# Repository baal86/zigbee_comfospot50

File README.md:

# Zigbee Comfospot 50
Hardware module to integrate Comfospot 50 ventilation system with ESP32-H2 zigbee enabled controller. Heavily based on https://github.com/lorenzspenger/comfospot-50 but using the ESP32-H2 and Zigbee.

## Hardware 
Contains a Kicad project to produce the hardware module that plugs inbetwen the Comfospot 50 main board and the user interface panel.

> The latest change to the hardware (shortening the PCB for mechanical fit) was not tested in production. I used a previous revision PCB and shortened it with a file. I will probably never produce the latest version.

## ESPHome
Contains the .yaml file to build the firmware using ESPHome. The `partitions_zb.csv` file is required at the time of writing for zigbee support! OTA is not supported by esphome-zigbee so the image must be programmed using a USB to serial (3.3V TTL levels) converter.

## zigbee2mqtt
Contains the external converter than needs to be provided to Zigbee2MQTT to recognize the device and present it to home assistant. It is currently very basic but is working and the fan unit can be controlled by selecting the desired step.

## TODO
Honestly, it works for me as is right now so don't expect any updates soon. Debugging is quite a pain due to the lack of OTA updates and wireless logging. What I could imagine:

- Support the filter change LED
- More advanced control of fan levels as in https://github.com/lorenzspenger/comfospot-50. My implementation is quite primitive.
- Support control of exhaust/circulation modes.

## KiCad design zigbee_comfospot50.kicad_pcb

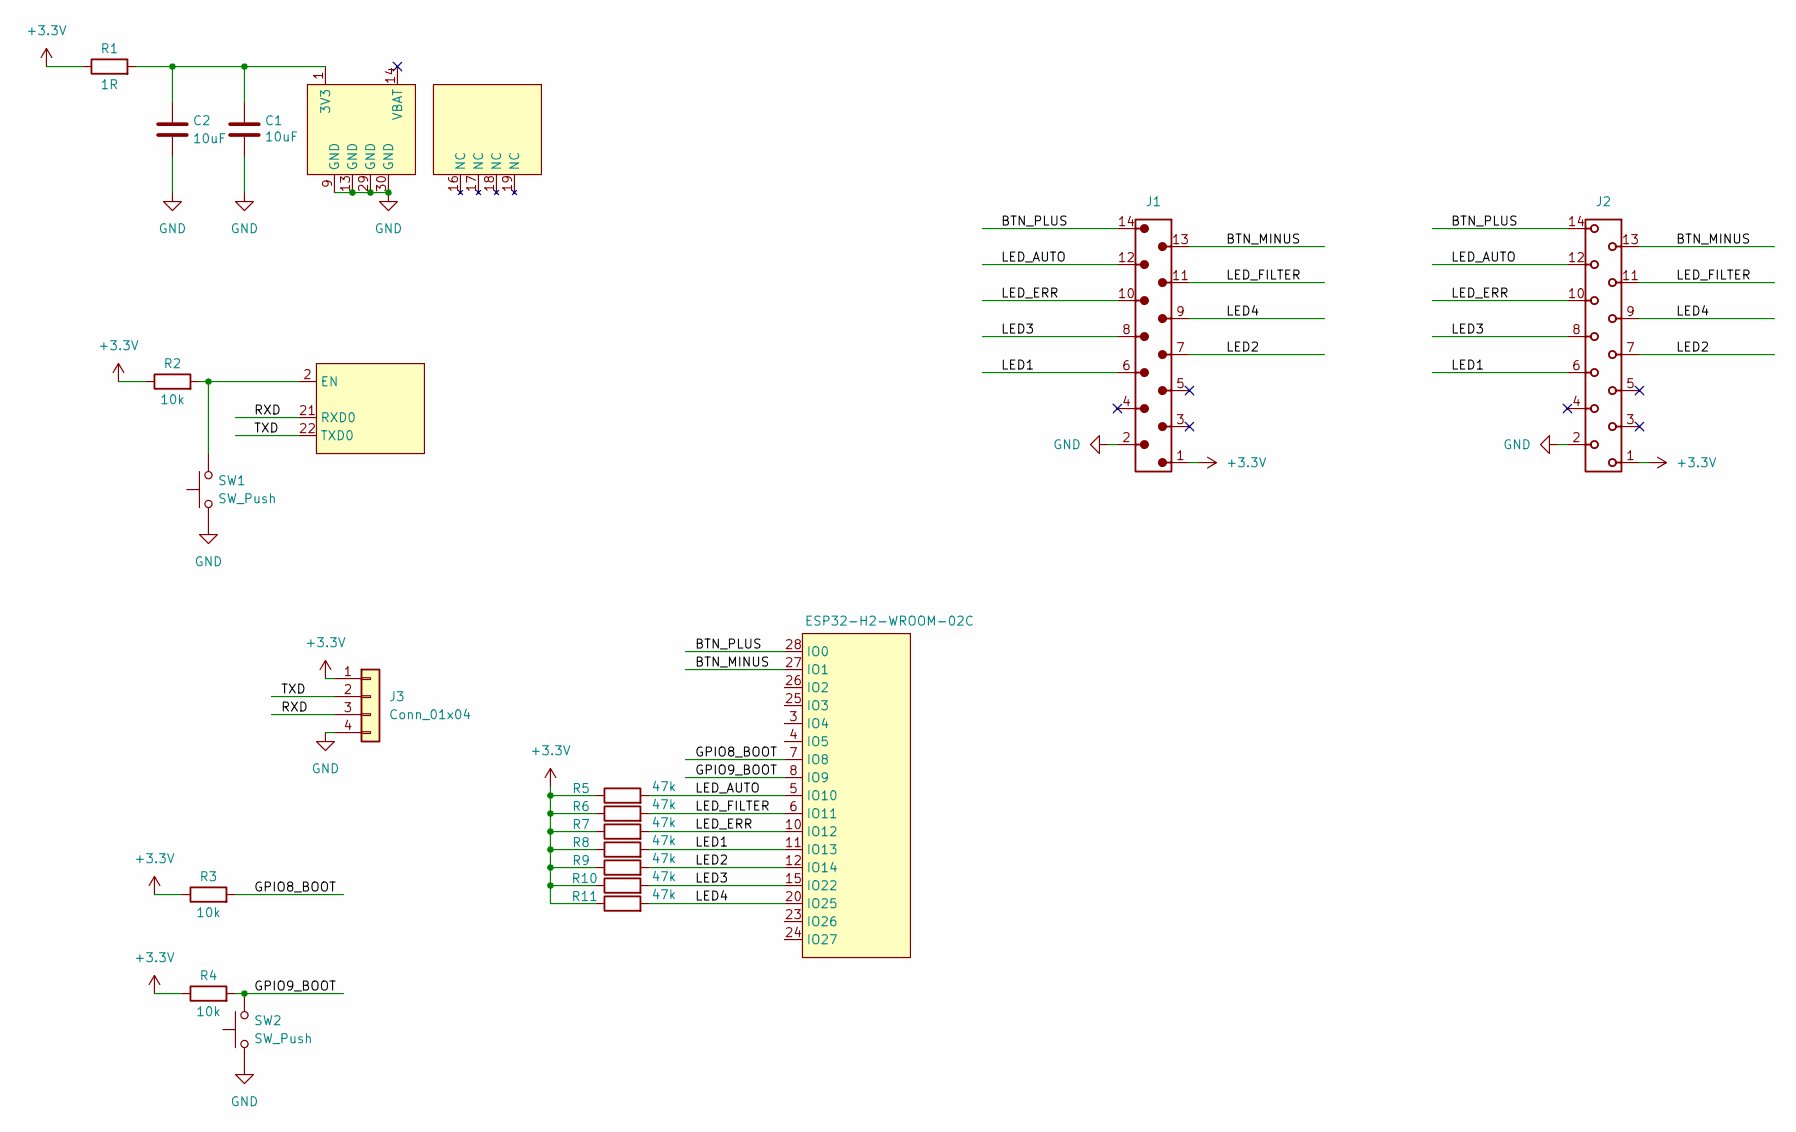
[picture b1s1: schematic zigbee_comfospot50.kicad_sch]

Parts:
C1, C2: 10uF; C_1206_3216Metric
J1: 690357101472; J_Wurth_WR-MM_690357101472
J2: 690367191472; J_Wurth_WR-MM_690367191472; Working Voltage (V (AC)) 250
J3: Conn_01x04; PinHeader_1x04_P2.54mm_Vertical
M1: (no value)
R1: 1R; R_0805_2012Metric
R2, R3, R4: 10k; R_0805_2012Metric
R5, R6, R7, R8, R9, R10, R11: 47k; R_0805_2012Metric
SW1, SW2: SW_Push; SW_Push_1P1T_NO_CK_KSC7xxJ
U1: ESP32-H2-WROOM-02C

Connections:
+3.3V: J1.1, J2.1, J3.1, R1.1, R2.1, R3.1, R4.1, R5.1, R6.1, R7.1, R8.1, R9.1, R10.1, R11.1
/BTN_MINUS: J1.13, J2.13, U1.27 (IO1)
/BTN_PLUS: J1.14, J2.14, U1.28 (IO0)
/GPIO8_BOOT: R3.2, U1.7 (IO8)
/GPIO9_BOOT: R4.2, SW2.2, U1.8 (IO9)
/LED1: J1.6, J2.6, R8.2, U1.11 (IO13)
/LED2: J1.7, J2.7, R9.2, U1.12 (IO14)
/LED3: J1.8, J2.8, R10.2, U1.15 (IO22)
/LED4: J1.9, J2.9, R11.2, U1.20 (IO25)
/LED_AUTO: J1.12, J2.12, R5.2, U1.5 (IO10)
/LED_ERR: J1.10, J2.10, R7.2, U1.10 (IO12)
/LED_FILTER: J1.11, J2.11, R6.2, U1.6 (IO11)
/RXD: J3.3, M1.21 (RXD0)
/TXD: J3.2, M1.22 (TXD0)
GND: C1.2, C2.2, J1.2, J2.2, J3.4, M1.9 (GND), M1.13 (GND), M1.29 (GND), M1.30 (GND), SW1.1, SW2.1
unnamed: C1.1, C2.1, M1.1 (3V3), R1.2
unnamed: M1.2 (EN), R2.2, SW1.2

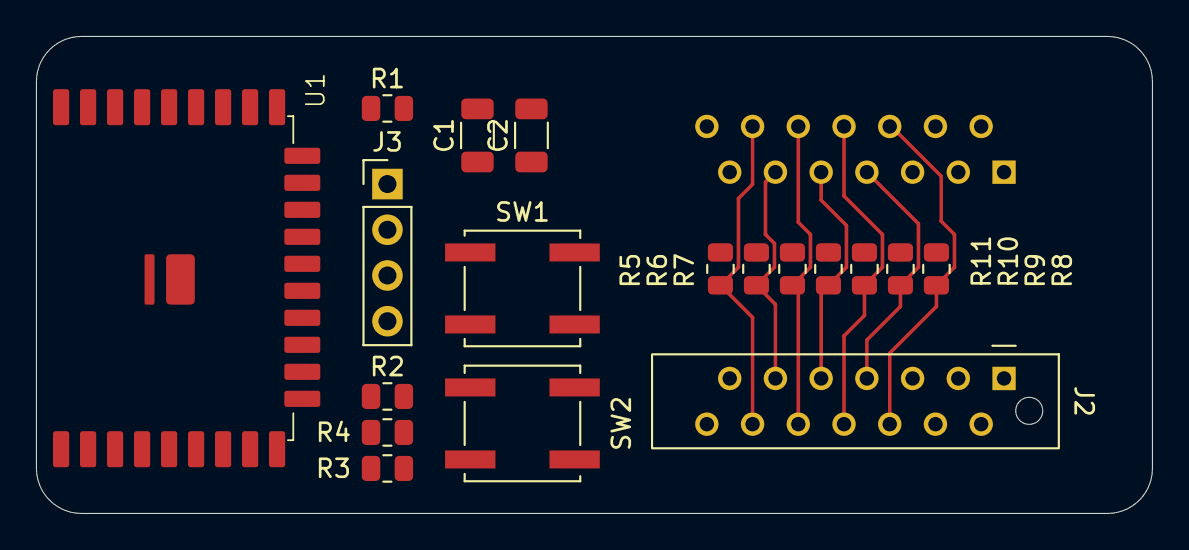
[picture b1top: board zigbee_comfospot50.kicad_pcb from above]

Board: 2 copper layers, 62.0 x 26.5 mm, 19 parts (1 on the bottom side), 15 nets.

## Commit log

2025-09-08 Added initial KiCAD Files
2025-09-08 Added local sym library
2025-09-08 Added H2 module
2025-09-08 added signal names
2025-09-08 add sym lib table
2025-09-08 Added Wurth FPS
2025-09-08 3D model
2025-09-09 Added correct connector
2025-09-09 Started routing
2025-09-09 ROuted
2025-09-28 Restructure
2025-09-28 Shortened PCB to fit Comfospot 50 available space. NOT YET TESTED in HW.
2025-12-23 Updated Z2M converter
2025-12-23 Delete Homeassistant/mqtt_template.yaml
    No longer required. Z2M converter now works!
2025-12-23 Add partitions_zb.csv for ESPHome configuration
    Required for esphome zigbee on H2.
2025-12-23 Enhance README with project details and TODO list
    Expanded README with detailed project information, including hardware, ESPHome, and zigbee2mqtt sections. Added TODO list for future improvements.
2025-12-23 Remove .DS_Store
2025-12-23 Added PCB render
2025-12-23 Update README.md
    Added picture of PCB
2026-01-05 Added PDF of schematics
